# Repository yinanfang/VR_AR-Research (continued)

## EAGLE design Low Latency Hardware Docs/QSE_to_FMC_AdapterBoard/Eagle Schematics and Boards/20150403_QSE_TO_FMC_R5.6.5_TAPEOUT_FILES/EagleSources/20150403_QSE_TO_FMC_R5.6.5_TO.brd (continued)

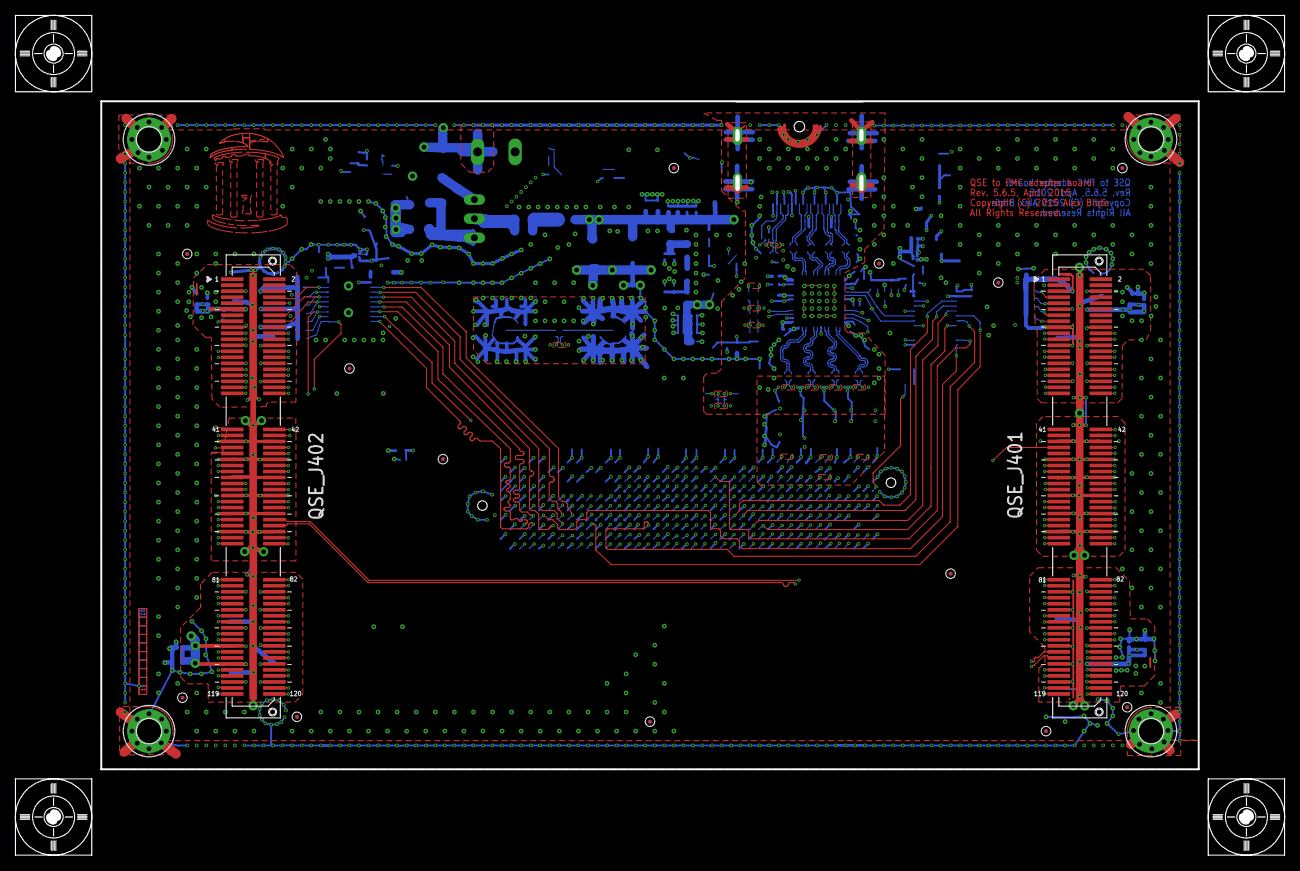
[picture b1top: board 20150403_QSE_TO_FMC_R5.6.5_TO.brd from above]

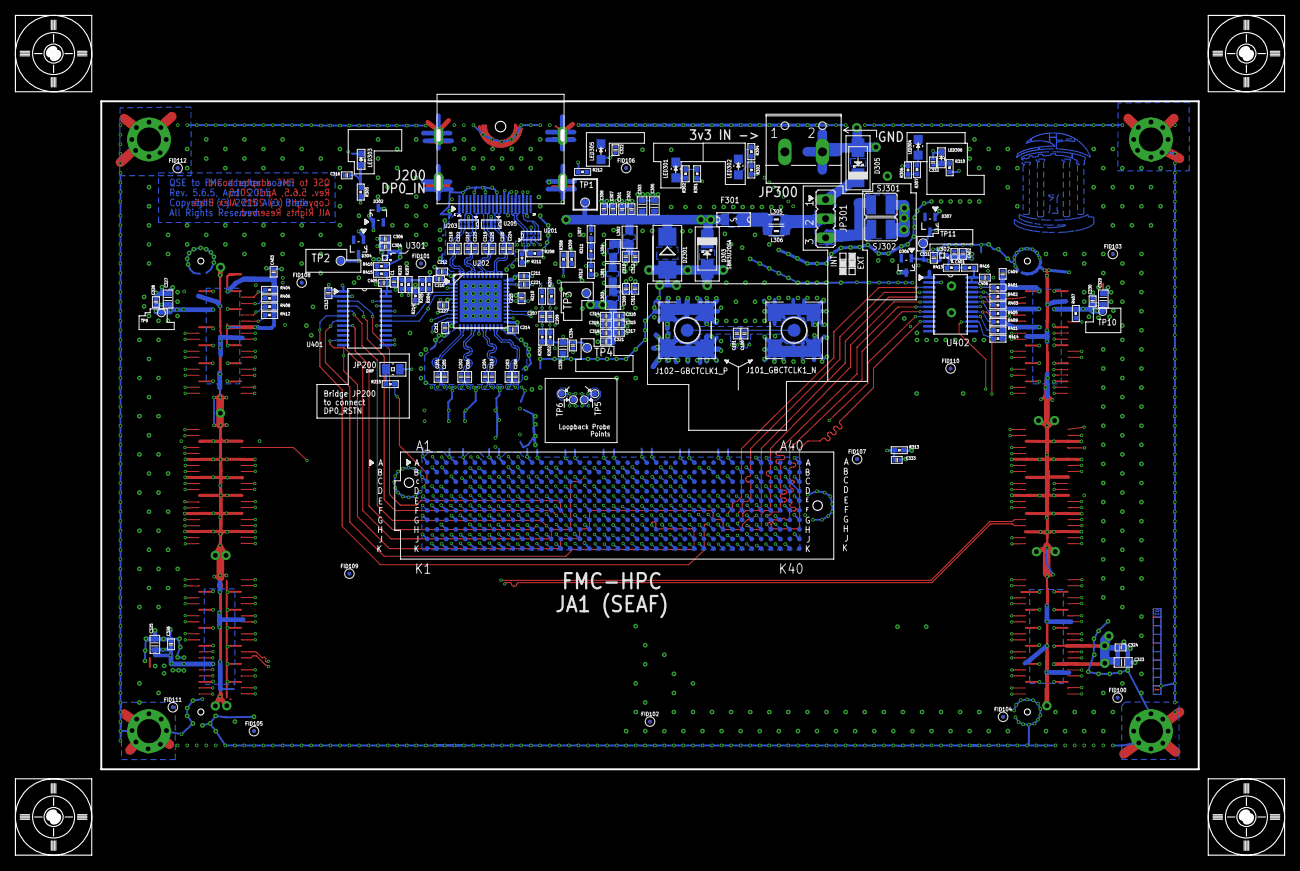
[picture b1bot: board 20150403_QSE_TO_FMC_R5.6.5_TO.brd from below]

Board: 10 copper layers, 146.1 x 88.9 mm, 185 parts (161 on the bottom side), 253 nets.

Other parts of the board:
FID100, FID101, FID102, FID103, FID104, FID105, FID106, FID107, FID108, FID109, FID110, FID111, FID112: FIDUTIAL
JA_FMC:JA1_FMC1: SEAF-40-10
QSE_J401: EXP1; QSE-060-01
QSE_J402: EXP2; QSE-060-01
U$8, U$9, U$10, U$11: ALIGNMENT

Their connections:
DP0_AUX_RX_DIFF_N: JA_FMC:JA1_FMC1.H11; also elsewhere on the board
DP0_AUX_RX_DIFF_P: JA_FMC:JA1_FMC1.H10; also elsewhere on the board
DP0_HPD: JA_FMC:JA1_FMC1.C18; also elsewhere on the board
DP0_LANE0_N: JA_FMC:JA1_FMC1.A11; also elsewhere on the board
DP0_LANE0_P: JA_FMC:JA1_FMC1.A10; also elsewhere on the board
DP0_LANE1_N: JA_FMC:JA1_FMC1.A7; also elsewhere on the board
DP0_LANE1_P: JA_FMC:JA1_FMC1.A6; also elsewhere on the board
DP0_LANE2_N: JA_FMC:JA1_FMC1.C7; also elsewhere on the board
DP0_LANE2_P: JA_FMC:JA1_FMC1.C6; also elsewhere on the board
DP0_LANE3_N: JA_FMC:JA1_FMC1.A3; also elsewhere on the board
DP0_LANE3_P: JA_FMC:JA1_FMC1.A2; also elsewhere on the board
DP0_RST: JA_FMC:JA1_FMC1.D1; also elsewhere on the board
DP0_RX_ENA: JA_FMC:JA1_FMC1.G36; also elsewhere on the board
DP0_RX_SENSE_N: JA_FMC:JA1_FMC1.G10; also elsewhere on the board
DP0_RX_SENSE_P: JA_FMC:JA1_FMC1.G9; also elsewhere on the board
DP0_SCL_CTL: JA_FMC:JA1_FMC1.H31; also elsewhere on the board
DP0_SDA_CTL: JA_FMC:JA1_FMC1.H25; also elsewhere on the board
EXP1_DIFF_CLK_IN_CLK2_N: JA_FMC:JA1_FMC1.K5, QSE_J401.44
EXP1_DIFF_CLK_IN_CLK2_P: JA_FMC:JA1_FMC1.K4, QSE_J401.42
EXP1_DIFF_CLK_OUT_CLK3_N: JA_FMC:JA1_FMC1.J3, QSE_J401.74
EXP1_DIFF_CLK_OUT_CLK3_P: JA_FMC:JA1_FMC1.J2, QSE_J401.72
EXP2_DIFF_CLK_IN_N: JA_FMC:JA1_FMC1.D21, QSE_J402.44
EXP2_DIFF_CLK_IN_P: JA_FMC:JA1_FMC1.D20, QSE_J402.42
EXP2_SE_CLK_IN: QSE_J402.43; also elsewhere on the board
EXP2_SE_CLK_IN_1V8: JA_FMC:JA1_FMC1.C22; also elsewhere on the board
FMC_3PV3_TERM: JA_FMC:JA1_FMC1.C39, JA_FMC:JA1_FMC1.D36, JA_FMC:JA1_FMC1.D38, JA_FMC:JA1_FMC1.D40; also elsewhere on the board
GBCTCLK1_M2C_N: JA_FMC:JA1_FMC1.B21; also elsewhere on the board
GBCTCLK1_M2C_P: JA_FMC:JA1_FMC1.B20; also elsewhere on the board
GND: JA_FMC:JA1_FMC1.A1, JA_FMC:JA1_FMC1.A4, JA_FMC:JA1_FMC1.A5, JA_FMC:JA1_FMC1.A8, JA_FMC:JA1_FMC1.A9, JA_FMC:JA1_FMC1.A12, JA_FMC:JA1_FMC1.A13, JA_FMC:JA1_FMC1.A16, JA_FMC:JA1_FMC1.A17, JA_FMC:JA1_FMC1.A20, JA_FMC:JA1_FMC1.A21, JA_FMC:JA1_FMC1.A24, JA_FMC:JA1_FMC1.A25, JA_FMC:JA1_FMC1.A28, JA_FMC:JA1_FMC1.A29, JA_FMC:JA1_FMC1.A32, JA_FMC:JA1_FMC1.A33, JA_FMC:JA1_FMC1.A36, JA_FMC:JA1_FMC1.A37, JA_FMC:JA1_FMC1.A40, JA_FMC:JA1_FMC1.B2, JA_FMC:JA1_FMC1.B3, JA_FMC:JA1_FMC1.B6, JA_FMC:JA1_FMC1.B7, JA_FMC:JA1_FMC1.B10, JA_FMC:JA1_FMC1.B11, JA_FMC:JA1_FMC1.B14, JA_FMC:JA1_FMC1.B15, JA_FMC:JA1_FMC1.B18, JA_FMC:JA1_FMC1.B19, JA_FMC:JA1_FMC1.B22, JA_FMC:JA1_FMC1.B23, JA_FMC:JA1_FMC1.B26, JA_FMC:JA1_FMC1.B27, JA_FMC:JA1_FMC1.B30, JA_FMC:JA1_FMC1.B31, JA_FMC:JA1_FMC1.B34, JA_FMC:JA1_FMC1.B35, JA_FMC:JA1_FMC1.B38, JA_FMC:JA1_FMC1.B39, JA_FMC:JA1_FMC1.C1, JA_FMC:JA1_FMC1.C4, JA_FMC:JA1_FMC1.C5, JA_FMC:JA1_FMC1.C8, JA_FMC:JA1_FMC1.C9, JA_FMC:JA1_FMC1.C12, JA_FMC:JA1_FMC1.C13, JA_FMC:JA1_FMC1.C16, JA_FMC:JA1_FMC1.C17, JA_FMC:JA1_FMC1.C20, JA_FMC:JA1_FMC1.C21, JA_FMC:JA1_FMC1.C23, JA_FMC:JA1_FMC1.C24, JA_FMC:JA1_FMC1.C25, JA_FMC:JA1_FMC1.C28, JA_FMC:JA1_FMC1.C29, JA_FMC:JA1_FMC1.C32, JA_FMC:JA1_FMC1.C33, JA_FMC:JA1_FMC1.C36, JA_FMC:JA1_FMC1.C38, JA_FMC:JA1_FMC1.C40, JA_FMC:JA1_FMC1.D2, JA_FMC:JA1_FMC1.D3, JA_FMC:JA1_FMC1.D6, JA_FMC:JA1_FMC1.D7, JA_FMC:JA1_FMC1.D10, JA_FMC:JA1_FMC1.D13, JA_FMC:JA1_FMC1.D16, JA_FMC:JA1_FMC1.D19, JA_FMC:JA1_FMC1.D22, JA_FMC:JA1_FMC1.D25, JA_FMC:JA1_FMC1.D28, JA_FMC:JA1_FMC1.D37, JA_FMC:JA1_FMC1.D39, JA_FMC:JA1_FMC1.E1, JA_FMC:JA1_FMC1.E4, JA_FMC:JA1_FMC1.E5, JA_FMC:JA1_FMC1.E8, JA_FMC:JA1_FMC1.E11, JA_FMC:JA1_FMC1.E14, JA_FMC:JA1_FMC1.E17, JA_FMC:JA1_FMC1.E20, JA_FMC:JA1_FMC1.E23, JA_FMC:JA1_FMC1.E26, JA_FMC:JA1_FMC1.E29, JA_FMC:JA1_FMC1.E32, JA_FMC:JA1_FMC1.E35, JA_FMC:JA1_FMC1.E38, JA_FMC:JA1_FMC1.E40, JA_FMC:JA1_FMC1.F2, JA_FMC:JA1_FMC1.F3, JA_FMC:JA1_FMC1.F6, JA_FMC:JA1_FMC1.F9, JA_FMC:JA1_FMC1.F12, JA_FMC:JA1_FMC1.F15, JA_FMC:JA1_FMC1.F18, JA_FMC:JA1_FMC1.F21, JA_FMC:JA1_FMC1.F24, JA_FMC:JA1_FMC1.F27, JA_FMC:JA1_FMC1.F30, JA_FMC:JA1_FMC1.F33, JA_FMC:JA1_FMC1.F36, JA_FMC:JA1_FMC1.F39, JA_FMC:JA1_FMC1.G1, JA_FMC:JA1_FMC1.G4, JA_FMC:JA1_FMC1.G5, JA_FMC:JA1_FMC1.G8, JA_FMC:JA1_FMC1.G11, JA_FMC:JA1_FMC1.G14, JA_FMC:JA1_FMC1.G17, JA_FMC:JA1_FMC1.G20, JA_FMC:JA1_FMC1.G23, JA_FMC:JA1_FMC1.G26, JA_FMC:JA1_FMC1.G29, JA_FMC:JA1_FMC1.G32, JA_FMC:JA1_FMC1.G35, JA_FMC:JA1_FMC1.G38, JA_FMC:JA1_FMC1.G40, JA_FMC:JA1_FMC1.H3, JA_FMC:JA1_FMC1.H6, JA_FMC:JA1_FMC1.H9, JA_FMC:JA1_FMC1.H12, JA_FMC:JA1_FMC1.H15, JA_FMC:JA1_FMC1.H18, JA_FMC:JA1_FMC1.H21, JA_FMC:JA1_FMC1.H24, JA_FMC:JA1_FMC1.H26, JA_FMC:JA1_FMC1.H27, JA_FMC:JA1_FMC1.H30, JA_FMC:JA1_FMC1.H32, JA_FMC:JA1_FMC1.H33, JA_FMC:JA1_FMC1.H36, JA_FMC:JA1_FMC1.H39, JA_FMC:JA1_FMC1.J1, JA_FMC:JA1_FMC1.J4, JA_FMC:JA1_FMC1.J5, JA_FMC:JA1_FMC1.J8, JA_FMC:JA1_FMC1.J11, JA_FMC:JA1_FMC1.J14, JA_FMC:JA1_FMC1.J17, JA_FMC:JA1_FMC1.J20, JA_FMC:JA1_FMC1.J23, JA_FMC:JA1_FMC1.J26, JA_FMC:JA1_FMC1.J29, JA_FMC:JA1_FMC1.J32, JA_FMC:JA1_FMC1.J35, JA_FMC:JA1_FMC1.J38, JA_FMC:JA1_FMC1.J40, JA_FMC:JA1_FMC1.K2, JA_FMC:JA1_FMC1.K3, JA_FMC:JA1_FMC1.K6, JA_FMC:JA1_FMC1.K9, JA_FMC:JA1_FMC1.K12, JA_FMC:JA1_FMC1.K15, JA_FMC:JA1_FMC1.K18, JA_FMC:JA1_FMC1.K21, JA_FMC:JA1_FMC1.K24, JA_FMC:JA1_FMC1.K27, JA_FMC:JA1_FMC1.K30, JA_FMC:JA1_FMC1.K33, JA_FMC:JA1_FMC1.K36, JA_FMC:JA1_FMC1.K39, QSE_J401.45, QSE_J401.46, QSE_J401.51, QSE_J401.52, QSE_J401.57, QSE_J401.58, QSE_J401.63, QSE_J401.64, QSE_J401.69, QSE_J401.70, QSE_J401.75, QSE_J401.76, QSE_J401.GND1, QSE_J401.GND2, QSE_J401.GND3, QSE_J401.GND4, QSE_J401.GND5, QSE_J401.GND6, QSE_J401.GND7, QSE_J401.GND8, QSE_J401.GND9, QSE_J401.GND10, QSE_J401.GND11, QSE_J401.GND12, QSE_J402.45, QSE_J402.46, QSE_J402.51, QSE_J402.52, QSE_J402.57, QSE_J402.58, QSE_J402.63, QSE_J402.64, QSE_J402.69, QSE_J402.70, QSE_J402.75, QSE_J402.76, QSE_J402.GND1, QSE_J402.GND2, QSE_J402.GND3, QSE_J402.GND4, QSE_J402.GND5, QSE_J402.GND6, QSE_J402.GND7, QSE_J402.GND8, QSE_J402.GND9, QSE_J402.GND10, QSE_J402.GND11, QSE_J402.GND12; also elsewhere on the board
GPIO_0: QSE_J402.41; also elsewhere on the board
GPIO_0_1V8: JA_FMC:JA1_FMC1.H37; also elsewhere on the board
GPIO_1: QSE_J402.47; also elsewhere on the board
GPIO_1_1V8: JA_FMC:JA1_FMC1.H38; also elsewhere on the board
GPIO_2: QSE_J402.14; also elsewhere on the board
GPIO_2_1V8: JA_FMC:JA1_FMC1.H34; also elsewhere on the board
GPIO_3: QSE_J402.16; also elsewhere on the board
GPIO_3_1V8: JA_FMC:JA1_FMC1.H35; also elsewhere on the board
GPIO_4: QSE_J402.10; also elsewhere on the board
GPIO_4_1V8: JA_FMC:JA1_FMC1.G34; also elsewhere on the board
GPIO_5: QSE_J402.8; also elsewhere on the board
GPIO_5_1V8: JA_FMC:JA1_FMC1.G33; also elsewhere on the board
GPIO_6: QSE_J401.13; also elsewhere on the board
GPIO_6_1V8: JA_FMC:JA1_FMC1.H14; also elsewhere on the board
GPIO_7: QSE_J401.15; also elsewhere on the board
GPIO_7_1V8: JA_FMC:JA1_FMC1.H13; also elsewhere on the board
GPIO_8: QSE_J401.7; also elsewhere on the board
GPIO_8_1V8: JA_FMC:JA1_FMC1.G16; also elsewhere on the board
GPIO_9: QSE_J401.9; also elsewhere on the board
GPIO_9_1V8: JA_FMC:JA1_FMC1.G15; also elsewhere on the board
GPIO_10: QSE_J402.15; also elsewhere on the board
GPIO_10_1V8: JA_FMC:JA1_FMC1.G37; also elsewhere on the board
HDP0_N: JA_FMC:JA1_FMC1.F5, QSE_J401.33
HDP0_P: JA_FMC:JA1_FMC1.F4, QSE_J401.31
HDP1_N: JA_FMC:JA1_FMC1.E3, QSE_J401.39
HDP1_P: JA_FMC:JA1_FMC1.E2, QSE_J401.37
HDP2_N: JA_FMC:JA1_FMC1.K8, QSE_J401.55
HDP2_P: JA_FMC:JA1_FMC1.K7, QSE_J401.53
HDP3_N: JA_FMC:JA1_FMC1.J7, QSE_J401.56
HDP3_P: JA_FMC:JA1_FMC1.J6, QSE_J401.54
HDP4_N: JA_FMC:JA1_FMC1.F8, QSE_J401.67
HDP4_P: JA_FMC:JA1_FMC1.F7, QSE_J401.65
HDP5_N: JA_FMC:JA1_FMC1.E7, QSE_J401.62
HDP5_P: JA_FMC:JA1_FMC1.E6, QSE_J401.60
HDP6_N: JA_FMC:JA1_FMC1.K11, QSE_J401.73
HDP6_P: JA_FMC:JA1_FMC1.K10, QSE_J401.71
HDP7_N: JA_FMC:JA1_FMC1.J10, QSE_J401.68
HDP7_P: JA_FMC:JA1_FMC1.J9, QSE_J401.66
HDP8_N: JA_FMC:JA1_FMC1.F11, QSE_J401.79
HDP8_P: JA_FMC:JA1_FMC1.F10, QSE_J401.77
HDP9_N: JA_FMC:JA1_FMC1.E10, QSE_J401.80
HDP9_P: JA_FMC:JA1_FMC1.E9, QSE_J401.78
HDP10_N: JA_FMC:JA1_FMC1.K14, QSE_J401.83
HDP10_P: JA_FMC:JA1_FMC1.K13, QSE_J401.81
HDP11_N: JA_FMC:JA1_FMC1.J13, QSE_J401.84
HDP11_P: JA_FMC:JA1_FMC1.J12, QSE_J401.82
HDP12_N: JA_FMC:JA1_FMC1.F14, QSE_J401.89
HDP12_P: JA_FMC:JA1_FMC1.F13, QSE_J401.87
HDP13_N: JA_FMC:JA1_FMC1.E13, QSE_J401.90
HDP13_P: JA_FMC:JA1_FMC1.E12, QSE_J401.88
HDP14_N: JA_FMC:JA1_FMC1.J16, QSE_J401.95
HDP14_P: JA_FMC:JA1_FMC1.J15, QSE_J401.93
HDP15_N: JA_FMC:JA1_FMC1.F17, QSE_J401.96
HDP15_P: JA_FMC:JA1_FMC1.F16, QSE_J401.94
HDP16_N: JA_FMC:JA1_FMC1.E16, QSE_J401.101
HDP16_P: JA_FMC:JA1_FMC1.E15, QSE_J401.99
HDP17_N: JA_FMC:JA1_FMC1.K17, QSE_J401.102
HDP17_P: JA_FMC:JA1_FMC1.K16, QSE_J401.100
HDP18_N: JA_FMC:JA1_FMC1.J19, QSE_J401.107
HDP18_P: JA_FMC:JA1_FMC1.J18, QSE_J401.105
HDP19_N: JA_FMC:JA1_FMC1.F20, QSE_J401.108
HDP19_P: JA_FMC:JA1_FMC1.F19, QSE_J401.106
HDP20_N: JA_FMC:JA1_FMC1.E19, QSE_J401.113
HDP20_P: JA_FMC:JA1_FMC1.E18, QSE_J401.111
HDP21_N: JA_FMC:JA1_FMC1.K20, QSE_J401.114
HDP21_P: JA_FMC:JA1_FMC1.K19, QSE_J401.112
HDP22_N: JA_FMC:JA1_FMC1.J22, QSE_J401.119
HDP22_P: JA_FMC:JA1_FMC1.J21, QSE_J401.117
HDP23_N: JA_FMC:JA1_FMC1.K23, QSE_J401.120
HDP23_P: JA_FMC:JA1_FMC1.K22, QSE_J401.118
HDQ0_N: JA_FMC:JA1_FMC1.K26, QSE_J402.120
HDQ0_P: JA_FMC:JA1_FMC1.K25, QSE_J402.118
HDQ1_N: JA_FMC:JA1_FMC1.J25, QSE_J402.119
HDQ1_P: JA_FMC:JA1_FMC1.J24, QSE_J402.117
HDQ2_N: JA_FMC:JA1_FMC1.F23, QSE_J402.114
HDQ2_P: JA_FMC:JA1_FMC1.F22, QSE_J402.112
HDQ3_N: JA_FMC:JA1_FMC1.E22, QSE_J402.113
HDQ3_P: JA_FMC:JA1_FMC1.E21, QSE_J402.111
HDQ4_N: JA_FMC:JA1_FMC1.F26, QSE_J402.108
HDQ4_P: JA_FMC:JA1_FMC1.F25, QSE_J402.106
HDQ5_N: JA_FMC:JA1_FMC1.E25, QSE_J402.107
HDQ5_P: JA_FMC:JA1_FMC1.E24, QSE_J402.105
HDQ6_N: JA_FMC:JA1_FMC1.K29, QSE_J402.102
HDQ6_P: JA_FMC:JA1_FMC1.K28, QSE_J402.100
HDQ7_N: JA_FMC:JA1_FMC1.J28, QSE_J402.101
HDQ7_P: JA_FMC:JA1_FMC1.J27, QSE_J402.99
HDQ8_N: JA_FMC:JA1_FMC1.F29, QSE_J402.96
HDQ8_P: JA_FMC:JA1_FMC1.F28, QSE_J402.94
HDQ9_N: JA_FMC:JA1_FMC1.E28, QSE_J402.95
HDQ9_P: JA_FMC:JA1_FMC1.E27, QSE_J402.93
HDQ10_N: JA_FMC:JA1_FMC1.K32, QSE_J402.90
HDQ10_P: JA_FMC:JA1_FMC1.K31, QSE_J402.88
HDQ11_N: JA_FMC:JA1_FMC1.J31, QSE_J402.89
HDQ11_P: JA_FMC:JA1_FMC1.J30, QSE_J402.87
HDQ12_N: JA_FMC:JA1_FMC1.F32, QSE_J402.84
HDQ12_P: JA_FMC:JA1_FMC1.F31, QSE_J402.82
HDQ13_N: JA_FMC:JA1_FMC1.E31, QSE_J402.83
HDQ13_P: JA_FMC:JA1_FMC1.E30, QSE_J402.81
HDQ14_N: JA_FMC:JA1_FMC1.K35, QSE_J402.80
HDQ14_P: JA_FMC:JA1_FMC1.K34, QSE_J402.78
HDQ15_N: JA_FMC:JA1_FMC1.J34, QSE_J402.79
HDQ15_P: JA_FMC:JA1_FMC1.J33, QSE_J402.77
HDQ16_N: JA_FMC:JA1_FMC1.F35, QSE_J402.68
HDQ16_P: JA_FMC:JA1_FMC1.F34, QSE_J402.66
HDQ17_N: JA_FMC:JA1_FMC1.K38, QSE_J402.73
HDQ17_P: JA_FMC:JA1_FMC1.K37, QSE_J402.71
HDQ18_N: JA_FMC:JA1_FMC1.J37, QSE_J402.62
HDQ18_P: JA_FMC:JA1_FMC1.J36, QSE_J402.60
HDQ19_N: JA_FMC:JA1_FMC1.E34, QSE_J402.67
HDQ19_P: JA_FMC:JA1_FMC1.E33, QSE_J402.65
HDQ20_N: JA_FMC:JA1_FMC1.F38, QSE_J402.56
HDQ20_P: JA_FMC:JA1_FMC1.F37, QSE_J402.54
HDQ21_N: JA_FMC:JA1_FMC1.E37, QSE_J402.55
HDQ21_P: JA_FMC:JA1_FMC1.E36, QSE_J402.53
LA00_N: JA_FMC:JA1_FMC1.G7, QSE_J401.61
LA00_P: JA_FMC:JA1_FMC1.G6, QSE_J401.59
LA01_N: JA_FMC:JA1_FMC1.D9, QSE_J401.50
LA01_P: JA_FMC:JA1_FMC1.D8, QSE_J401.48
LA02_N: JA_FMC:JA1_FMC1.H8, QSE_J402.74
LA02_P: JA_FMC:JA1_FMC1.H7, QSE_J402.72
LA05_N: JA_FMC:JA1_FMC1.D12, QSE_J401.34
LA05_P: JA_FMC:JA1_FMC1.D11, QSE_J401.32
LA06_N: JA_FMC:JA1_FMC1.C11, QSE_J401.40
LA06_P: JA_FMC:JA1_FMC1.C10, QSE_J401.38
LA08_N: JA_FMC:JA1_FMC1.G13, QSE_J401.28
LA08_P: JA_FMC:JA1_FMC1.G12, QSE_J401.26
LA09_N: JA_FMC:JA1_FMC1.D15, QSE_J401.22
LA09_P: JA_FMC:JA1_FMC1.D14, QSE_J401.20
LA10_N: JA_FMC:JA1_FMC1.C15, QSE_J401.27
LA10_P: JA_FMC:JA1_FMC1.C14, QSE_J401.25
LA13_N: JA_FMC:JA1_FMC1.D18, QSE_J401.21
LA13_P: JA_FMC:JA1_FMC1.D17, QSE_J401.19
LA16_N: JA_FMC:JA1_FMC1.G19, QSE_J402.50
LA16_P: JA_FMC:JA1_FMC1.G18, QSE_J402.48
LA19_N: JA_FMC:JA1_FMC1.H23, QSE_J402.39
LA19_P: JA_FMC:JA1_FMC1.H22, QSE_J402.37
LA20_N: JA_FMC:JA1_FMC1.G22, QSE_J402.22
LA20_P: JA_FMC:JA1_FMC1.G21, QSE_J402.20
LA22_N: JA_FMC:JA1_FMC1.G25, QSE_J402.28
LA22_P: JA_FMC:JA1_FMC1.G24, QSE_J402.26
LA23_N: JA_FMC:JA1_FMC1.D24, QSE_J402.21
LA23_P: JA_FMC:JA1_FMC1.D23, QSE_J402.19
LA24_N: JA_FMC:JA1_FMC1.H29, QSE_J402.61
LA24_P: JA_FMC:JA1_FMC1.H28, QSE_J402.59
LA25_N: JA_FMC:JA1_FMC1.G28, QSE_J402.27
LA25_P: JA_FMC:JA1_FMC1.G27, QSE_J402.25
LA26_N: JA_FMC:JA1_FMC1.D27, QSE_J402.34
LA26_P: JA_FMC:JA1_FMC1.D26, QSE_J402.32
LA27_N: JA_FMC:JA1_FMC1.C27, QSE_J402.33
LA27_P: JA_FMC:JA1_FMC1.C26, QSE_J402.31
LA29_N: JA_FMC:JA1_FMC1.G31, QSE_J402.40
LA29_P: JA_FMC:JA1_FMC1.G30, QSE_J402.38
LOOP0_N: JA_FMC:JA1_FMC1.H17, JA_FMC:JA1_FMC1.H20; also elsewhere on the board
LOOP0_P: JA_FMC:JA1_FMC1.H16, JA_FMC:JA1_FMC1.H19; also elsewhere on the board
PG_M2C: JA_FMC:JA1_FMC1.F1, QSE_J401.47
VCC_EXP1_2V5: QSE_J401.5, QSE_J401.6, QSE_J401.11, QSE_J401.12, QSE_J401.17, QSE_J401.18, QSE_J401.23, QSE_J401.24, QSE_J401.29, QSE_J401.30, QSE_J401.35, QSE_J401.36; also elsewhere on the board
VCC_EXP1_3V3: QSE_J401.85, QSE_J401.86, QSE_J401.91, QSE_J401.92, QSE_J401.97, QSE_J401.98, QSE_J401.103, QSE_J401.104, QSE_J401.109, QSE_J401.110, QSE_J401.115, QSE_J401.116; also elsewhere on the board
VCC_EXP2_2V5: QSE_J402.5, QSE_J402.6, QSE_J402.11, QSE_J402.12, QSE_J402.17, QSE_J402.18, QSE_J402.23, QSE_J402.24, QSE_J402.29, QSE_J402.30, QSE_J402.35, QSE_J402.36; also elsewhere on the board
VCC_EXP2_3V3: QSE_J402.85, QSE_J402.86, QSE_J402.91, QSE_J402.92, QSE_J402.97, QSE_J402.98, QSE_J402.103, QSE_J402.104, QSE_J402.109, QSE_J402.110, QSE_J402.115, QSE_J402.116; also elsewhere on the board

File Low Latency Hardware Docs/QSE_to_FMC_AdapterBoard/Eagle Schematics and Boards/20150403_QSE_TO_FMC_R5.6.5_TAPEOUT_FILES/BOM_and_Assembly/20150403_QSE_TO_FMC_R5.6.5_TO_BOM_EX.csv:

"Qty","Value","Part Num","Package","Parts","Mfg Name","VID","Vendor Part Num","Description","Pkg Code","XREF"
"1","","395443002","W237-102","JP300","Molex","DK","WM7853-ND","CONN TERMINAL BLOCK 2POS 5.08MM","*","REF13"
"1","1.5K OHMS","CRCW04021K50FKED","RESC1005X40N","R312","Vishay Dale","DK","541-1.50KLCT-ND","RES SMD 1.5K OHM 1% 1/16W 0402","0402","REF24"
"1","1M OHM","CRCW04021M00DHEDP","RESC1005X40N","R313","Vishay Dale","DK","541-1.0MAVCT-ND","RES SMD 1M OHM 0.5% 1/16W 0402","0402","REF22"
"2","1M OHMS","CRCW04021M00DHEDP","RESC1005X40N","R208, R211","Vishay Dale","DK","541-1.0MAVCT-ND","RES SMD 1M OHM 0.5% 1/16W 0402","0402","REF22"
"6","1NF","GRM1555C1H102JA01D","CAPC1005X60N","C307, C308, C311, C312, C318, C319","Murata Electronics North America","DK","490-3244-1-ND","1n NP0 Cap","CAPC1005X60N","REF5"
"14","1UF","GRM155R61A105KE15D","CAPC1005X60N","C216, C221, C304, C313, C316, C320, C321, C322, C331, C332, C333, C402, C405, C406","Murata Electronics North America","DK","490-3890-1-ND","1u X5R 0402 Cap","CAPC1005X60N","REF2"
"16","2.49K OHMS","CRCW04021K50FKED","RESC1005X40N","R203, R204, R205, R207, R401, R402, R403, R404, R405, R406, R407, R408, R409, R411, R412, R414","Vishay Dale","DK","541-1.50KLCT-ND","RES SMD 1.5K OHM 1% 1/16W 0402","0402","REF24"
"1","2.49K OHMS","CRCW04022K49FKED","RESC1005X40N","R311","Vishay Dale","DK","541-2.49KLCT-ND","RES SMD 2.49K OHM 1% 1/16W 0402","0402","REF27"
"1","3.6V","1SMB5914BT3G","SMB","DZ301","ON Semiconductor","DK","1SMB5914BT3GOSCT-ND","DIODE ZENER 3.6V 3W SMB/DO214-AA","SMB","REF8"
"1","3V3_SRC","901200763","JP2","JP301","Molex","DK","WM8085-ND","CONN HEADER 3POS .100"" STR GOLD","*","REF14"
"3","10K OHMS","CRCW040210K0JNEDHP","RESC1005X40N","R209, R210, R215","Vishay Dale","DK","541-10KYACT-ND","RES SMD 10K OHM 5% 1/8W 0402","0402","REF25"
"11","10NF","GRM155R71E103KA01D","CAPC1005X60N","C301, C302, C306, C315, C317, C324, C326, C328, C330, C334, C401","Murata Electronics North America","DK","490-1312-1-ND","10n X7R 0402 Cap","CAPC1005X60N","REF3"
"7","10UF","GRM188R60J106ME47D","CAPC1608X85N","C303, C305, C323, C325, C327, C329, C335","Murata Electronics North America","DK","490-3896-1-ND","10u X5R 0603 Cap","CAPC1608X85N","REF4"
"12","49.9R","TNPW040249R9BEED","RESC1005X40N","R201, R202, R301, R302, R303, R304, R305, R306, R307, R308, R309, R310","Vishay Dale","DK","TNP49.9DACT-ND","RES SMD 49.9 OHM 0.1% 1/16W 0402","0402","REF23"
"6","100K OHMS","CRCW0402100KFKED","RESC1005X40N","R212, R214, R410, R413, R415, R416","Vishay Dale","DK","541-100KLCT-ND","RES SMD 100K OHM 1% 1/16W 0402","0402","REF26"
"32","100NF","GRM155R71C104KA88D","CAPC1005X60N","C1, C100, C101, C201, C202, C203, C204, C205, C206, C207, C208, C209, C210, C211, C212, C213, C214, C215, C217, C218, C219, C220, C222, C223, C224, C225, C227, C309, C310, C314, C403, C404","Murata Electronics North America","DK","490-3261-1-ND","100n X7R 0402 Cap","CAPC1005X60N","REF1"
"4","BAT54W","BAT54W-7-F","SOT65P210X100-3N","D302, D304, D306, D307","Diodes Incorporated","DK","BAT54W-FDICT-ND","DIODE SCHOTTKY 30V 200MA SOT323","SOT323","REF7"
"1","DP0_IN","472720001","SD-47272","J200","Molex","DK","WM19271CT-ND","DisplayPort CONN RCPT 20POS UDI R/A SMD","*","REF12"
"1","EXP1","QSE-060-01-L-D-A","QSE-060-01","QSE_J401","Samtec, Inc","DK","SAM8125-ND","CONN RCPT HI-SPEED DUAL 120PO","*","REF21"
"1","EXP2","QSE-060-01-L-D-A","QSE-060-01","QSE_J402","Samtec, Inc","DK","SAM8125-ND","CONN RCPT HI-SPEED DUAL 120PO","*","REF21"
"2","FB","742792097","0805","L305, L306","Wurth Electronics Inc","DK","732-4649-1-ND","WE-CBF SMD EMI SUPP FERRITE BEAD","0805","REF17"
"1","FB","742841210","0402","L307","Wurth Electronics Inc","DK","732-2363-1-ND","FERRITE BEAD 1000 OHM .05A 0402","0402","REF16"
"2","FILT","BLM18HE152SN1D","R0603","L302, L304","Murata Electronics North America","DK","490-5216-1-ND","FERRITE CHIP 1500 OHM 500MA 0603","0603","REF15"
"2","FILT","BLM18HE601SN1D","R0603","L301, L303","Murata Electronics North America","DK","490-5214-1-ND","FERRITE CHIP 600 OHM 800MA 0603","0603","REF18"
"4","GREEN","LG R971-KN-1","CHIP-LED0805","LED301, LED302, LED304, LED305","OSRAM Opto Semiconductors Inc","DK","475-1410-1-ND","LED CHIPLED 570NM GREEN 0805 SMD","0805","REF19"
"2","LP5907SNX-1.8/NOPB","LP5907SNX-1.8/NOPB","YKE4","U301, U302","Texas Instruments","ME","595-LP5907SNX-1.8NPB","LDO Voltage Regulators 250mA Ultra-Lo Noise LDO Reg","YKE4","REF32"
"1","PTC_0A5","MF-PSMF050X-2","SMD-0805","F301","Bourns Inc","DK","MF-PSMF050X-2CT-ND","FUSE 0.5A PTC RESETTABLE SMD 0805","0805","REF9"
"2","RED","5975112407F","SML0603","LED303, LED306","Dialight","DK","350-2436-6-ND","LED RED ALGAAS 647NM WH DIFF","0603","REF20"
"2","SBR3U20SA","SBR3U20SA-13","SMA","D303, D305","Diodes Incorporated","ME","621-SBR3U20SA-13","Schottky Diode SMA/DO-214AC","SMA","REF6"
"1","SEAF-40-10","45971-4315","SEAF-40-10","JA_FMC:JA1_FMC1","Molex","ME","538-45971-4315","Board to Board & Mezzanine Connectors ","*","REF10"
"2","SMA-SMD","132134-10","SMA-SMD","J101_GBCTCLK1_N, J102-GBCTCLK1_P","Amphenol Connex","ME","523-132134-10","RF Connectors / Coaxial Connectors SMA SURFACE MOUNT JACK","*","REF11"
"2","SN74GTL2010","SN74GTL2010PW","PW24","U401, U402","Texas Instruments","DK","296-33915-5-ND","IC VOLTAGE CLAMP 10BIT 24-TSSOP","24-TSSOP","REF30"
"1","SN75DP130","SN75DP130SSRGZR","RGZ48_5P6X5P6","U202","Texas Instruments","DK","296-29377-1-ND","IC DISPLYPRT 1:1 REDRIVR 48VQFN","48-VQFN","REF29"
"3","TPD4S010_DQA_10","TPD4S010DQAR","DQA10","U201, U203, U205","Texas Instruments","DK","296-24177-1-ND","TVS DIODE 5.5VWM 10SON (DP ESD)","10-SON","REF28"

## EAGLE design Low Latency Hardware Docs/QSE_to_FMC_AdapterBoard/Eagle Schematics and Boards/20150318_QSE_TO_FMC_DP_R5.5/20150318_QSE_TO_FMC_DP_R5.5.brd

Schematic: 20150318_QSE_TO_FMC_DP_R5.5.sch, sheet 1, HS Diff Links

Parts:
C100, C101: 100nF; CAPC1005X60N
C102: 1uF; CAPC1005X60N; PART# GRM188B31A225KE33
H1, H2, H3, H4: MOUNT-PAD-ROUND3.2; 3,2-PAD
J101: GBCTCLK1 N; SMA-SMD; MPN 132134-10; DIGIKEY_SKU 132134-10-ND
J102: GBCTCLK1_P; SMA-SMD; MPN 132134-10; DIGIKEY_SKU 132134-10-ND
R100: 1M; RESC1005X40N
TP5: LOOP0_N; TP06R
TP6: LOOP0_P; TP06R
TP7, TP8: GND; TP06R

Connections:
FMC_3PV3_TERM: C102.2 (1), R100.1; also elsewhere on the board
GBCTCLK1_M2C_C_N: C100.1 (2), J101.1
GBCTCLK1_M2C_C_P: C101.1 (2), J102.1
GBCTCLK1_M2C_N: C100.2 (1); also elsewhere on the board
GBCTCLK1_M2C_P: C101.2 (1); also elsewhere on the board
GND: C102.1 (2), H1.B3,2, H2.B3,2, H3.B3,2, H4.B3,2, J101.2@1 (2), J101.2@2 (2), J101.2@3 (2), J101.2@4 (2), J101.2@5 (2), J101.2@6 (2), J102.2@1 (2), J102.2@2 (2), J102.2@3 (2), J102.2@4 (2), J102.2@5 (2), J102.2@6 (2), R100.2, TP7.TP, TP8.TP; also elsewhere on the board
LOOP0_N: TP5.TP; also elsewhere on the board
LOOP0_P: TP6.TP; also elsewhere on the board

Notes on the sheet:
3.2mm mounting holes, tied to ground plane.
V7 Bank 37
V7 Bank 12
V7 Bank 38
V7 Bank 39
Low-speed (enable/detect)
High-speed Connectors
V7 Bank 111
QSE1/QSE2
Not Used
We only draw from the EXP2 3v3 power rail. The others are terminated to power planes and decoupled.
^ LVCMOS_18 ^
^ LVCMOS_18 ^ PULLUP
^ LVDS ^
V7 Bank 111 Optional external clock reference
Connect/terminate to 50 ohms at transmitter

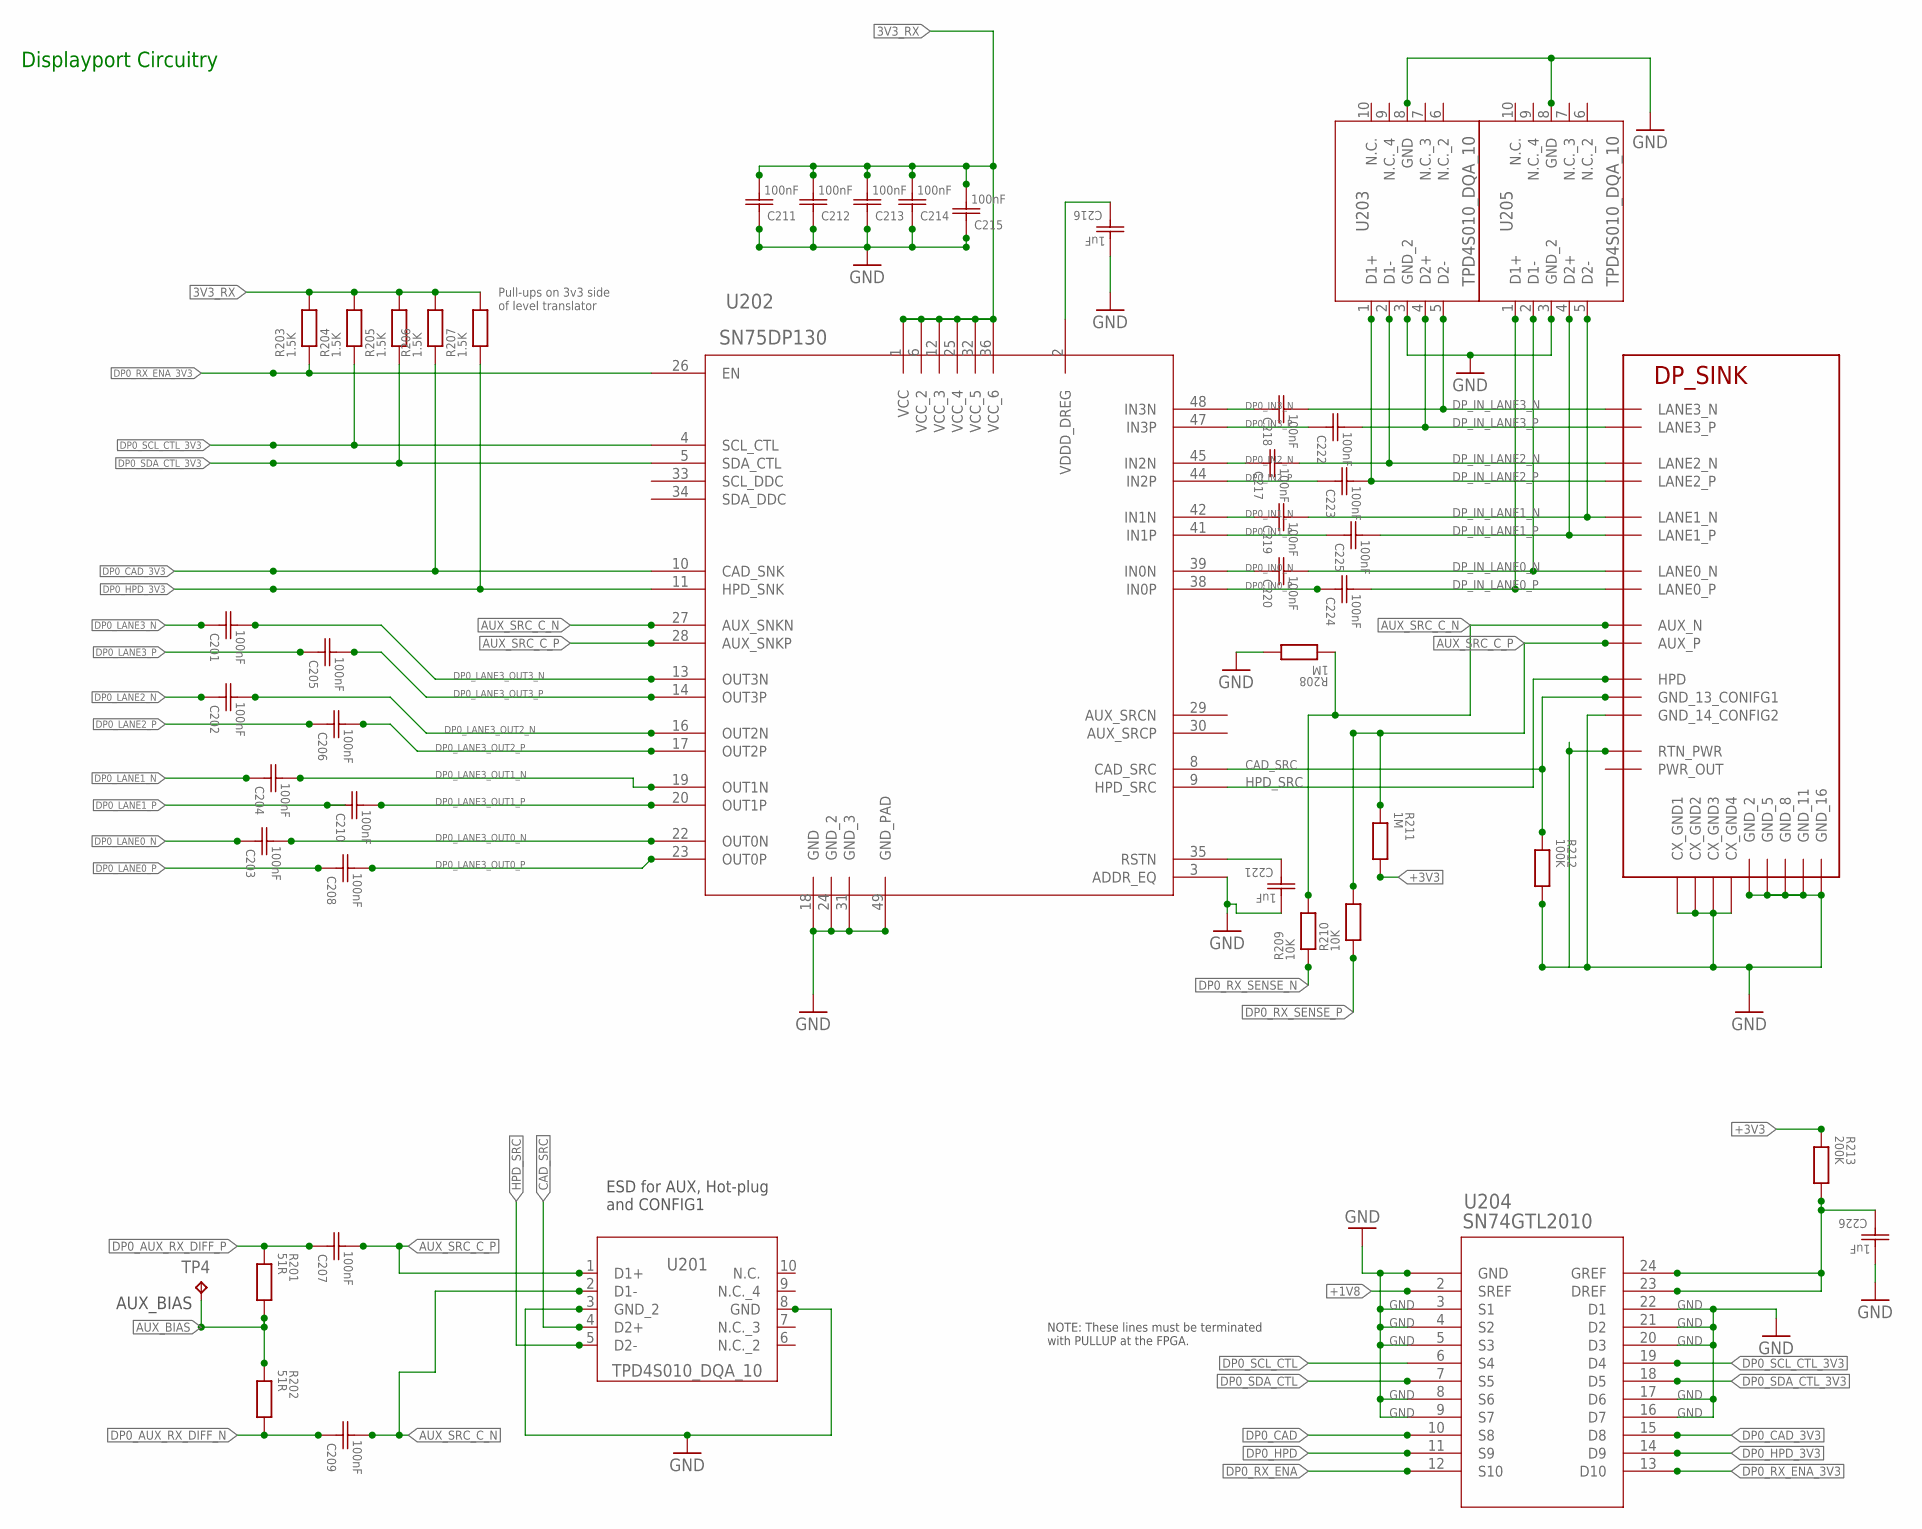
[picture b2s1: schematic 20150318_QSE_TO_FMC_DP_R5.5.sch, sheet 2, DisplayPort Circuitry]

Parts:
C201, C202, C203, C204, C205, C206, C207, C208, C209, C210, C217, C218, C219, C220, C222, C223, C224, C225: 100nF; CAPC1005X60N
C211, C212, C213, C214, C215: 100nF; CAPC1005X60N; PART# GRM188B31H104MA92
C216, C221, C226: 1uF; CAPC1005X60N; PART# GRM188B31A225KE33
R201, R202: 51R; RESC1005X40N
R203, R204, R205, R206, R207: 1.5K; RESC1005X40N
R208, R211: 1M; RESC1005X40N
R209, R210: 10K; RESC1005X40N
R212: 100K; RESC1005X40N
R213: 200K; RESC1005X40N
TP4: AUX_BIAS; TP10R
U201, U203, U205: TPD4S010_DQA_10; DQA10
U202: SN75DP130; RGZ48_5P6X5P6
U204: SN74GTL2010; PW24
U206: DP0_IN; SD-47272

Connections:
3V3_RX: C211.1 (2), C212.1 (2), C213.1 (2), C214.1 (2), C215.1 (2), R203.1, R204.1, R205.1, R206.1, R207.1, U202.1 (VCC), U202.6 (VCC_2), U202.12 (VCC_3), U202.25 (VCC_4), U202.32 (VCC_5), U202.36 (VCC_6); also elsewhere on the board
+1V8: U204.2 (SREF); also elsewhere on the board
+3V3: R211.1, R213.2; also elsewhere on the board
AUX_BIAS: R201.1, R202.2, TP4.TP; also elsewhere on the board
AUX_SRC_C_N: C209.1 (2), R208.2, R209.1, U201.2 (D1-), U202.27 (AUX_SNKN), U206.P$17 (AUX_N)
AUX_SRC_C_P: C207.1 (2), R210.1, R211.2, U201.1 (D1+), U202.28 (AUX_SNKP), U206.P$15 (AUX_P)
CAD_SRC: R212.2, U201.4 (D2+), U202.8 (CAD_SRC), U206.P$13 (GND_13_CONIFG1)
DP0_AUX_RX_DIFF_N: C209.2 (1), R202.1; also elsewhere on the board
DP0_AUX_RX_DIFF_P: C207.2 (1), R201.2; also elsewhere on the board
DP0_CAD: U204.10 (S8); also elsewhere on the board
DP0_CAD_3V3: R206.2, U202.10 (CAD_SNK), U204.15 (D8)
DP0_HPD: U204.11 (S9); also elsewhere on the board
DP0_HPD_3V3: R207.2, U202.11 (HPD_SNK), U204.14 (D9)
DP0_IN0_N: C220.2 (1), U202.39 (IN0N)
DP0_IN0_P: C224.2 (1), U202.38 (IN0P)
DP0_IN1_N: C219.2 (1), U202.42 (IN1N)
DP0_IN1_P: C225.2 (1), U202.41 (IN1P)
DP0_IN2_N: C217.2 (1), U202.45 (IN2N)
DP0_IN2_P: C223.2 (1), U202.44 (IN2P)
DP0_IN3_N: C218.2 (1), U202.48 (IN3N)
DP0_IN3_P: C222.2 (1), U202.47 (IN3P)
DP0_LANE0_N: C203.2 (1); also elsewhere on the board
DP0_LANE0_P: C208.2 (1); also elsewhere on the board
DP0_LANE1_N: C204.2 (1); also elsewhere on the board
DP0_LANE1_P: C210.2 (1); also elsewhere on the board
DP0_LANE2_N: C202.2 (1); also elsewhere on the board
DP0_LANE2_P: C206.2 (1); also elsewhere on the board
DP0_LANE3_N: C201.2 (1); also elsewhere on the board
DP0_LANE3_OUT0_N: C203.1 (2), U202.22 (OUT0N)
DP0_LANE3_OUT0_P: C208.1 (2), U202.23 (OUT0P)
DP0_LANE3_OUT1_N: C204.1 (2), U202.19 (OUT1N)
DP0_LANE3_OUT1_P: C210.1 (2), U202.20 (OUT1P)
DP0_LANE3_OUT2_N: C202.1 (2), U202.16 (OUT2N)
DP0_LANE3_OUT2_P: C206.1 (2), U202.17 (OUT2P)
DP0_LANE3_OUT3_N: C201.1 (2), U202.13 (OUT3N)
DP0_LANE3_OUT3_P: C205.1 (2), U202.14 (OUT3P)
DP0_LANE3_P: C205.2 (1); also elsewhere on the board
DP0_RX_ENA: U204.12 (S10); also elsewhere on the board
DP0_RX_ENA_3V3: R203.2, U202.26 (EN), U204.13 (D10)
DP0_RX_SENSE_N: R209.2; also elsewhere on the board
DP0_RX_SENSE_P: R210.2; also elsewhere on the board
DP0_SCL_CTL: U204.6 (S4); also elsewhere on the board
DP0_SCL_CTL_3V3: R204.2, U202.4 (SCL_CTL), U204.19 (D4)
DP0_SDA_CTL: U204.7 (S5); also elsewhere on the board
DP0_SDA_CTL_3V3: R205.2, U202.5 (SDA_CTL), U204.18 (D5)
DP_IN_LANE0_N: C220.1 (2), U205.2 (D1-), U206.P$10 (LANE0_N)
DP_IN_LANE0_P: C224.1 (2), U205.1 (D1+), U206.P$12 (LANE0_P)
DP_IN_LANE1_N: C219.1 (2), U205.5 (D2-), U206.P$7 (LANE1_N)
DP_IN_LANE1_P: C225.1 (2), U205.4 (D2+), U206.P$9 (LANE1_P)
DP_IN_LANE2_N: C217.1 (2), U203.2 (D1-), U206.P$4 (LANE2_N)
DP_IN_LANE2_P: C223.1 (2), U203.1 (D1+), U206.P$6 (LANE2_P)
DP_IN_LANE3_N: C218.1 (2), U203.5 (D2-), U206.P$1 (LANE3_N)
DP_IN_LANE3_P: C222.1 (2), U203.4 (D2+), U206.P$3 (LANE3_P)
GND: C211.2 (1), C212.2 (1), C213.2 (1), C214.2 (1), C215.2 (1), C216.1 (2), C221.1 (2), C226.1 (2), R208.1, R212.1, U201.3 (GND_2), U201.8 (GND), U202.3 (ADDR_EQ), U202.18 (GND), U202.24 (GND_2), U202.31 (GND_3), U202.49 (GND_PAD), U203.3 (GND_2), U203.8 (GND), U204.1 (GND), U204.3 (S1), U204.4 (S2), U204.5 (S3), U204.8 (S6), U204.9 (S7), U204.16 (D7), U204.17 (D6), U204.20 (D3), U204.21 (D2), U204.22 (D1), U205.3 (GND_2), U205.8 (GND), U206.P$2 (GND_2), U206.P$5 (GND_5), U206.P$8 (GND_8), U206.P$11 (GND_11), U206.P$14 (GND_14_CONFIG2), U206.P$16 (GND_16), U206.P$19 (RTN_PWR), U206.P$21 (CX_GND1), U206.P$22 (CX_GND2), U206.P$23 (CX_GND3), U206.P$24 (CX_GND4); also elsewhere on the board
HPD_SRC: U201.5 (D2-), U202.9 (HPD_SRC), U206.P$18 (HPD)
PWR_OUT: U206.P$20 (PWR_OUT)
RSTN_SOFT_START: C221.2 (1), U202.35 (RSTN)
VDDD_DREG_DECOUPLE: C216.2 (1), U202.2 (VDDD_DREG)
XLAT_3V3_BIAS: C226.2 (1), R213.1, U204.23 (DREF), U204.24 (GREF)

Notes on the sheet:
NOTE: These lines must be terminated with PULLUP at the FPGA.
ESD for AUX, Hot-plug and CONFIG1
Displayport Circuitry
Pull-ups on 3v3 side of level translator
